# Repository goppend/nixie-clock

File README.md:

# Nixie Tube Clock (wip)

A nixie clock using IN-12 tubes, featuring a modular and efficient design.

## Todo
- [x] Port what I have to KiCad.
- [x] Fix existing problems.
- [x] Consider design changes, add last minute features, ERC.
- [x] Ensure layout is sound. DRC.
- [x] Have boards fabbed.
- [ ] (Awaiting boards/parts) Write firmware.
- [ ] Done!

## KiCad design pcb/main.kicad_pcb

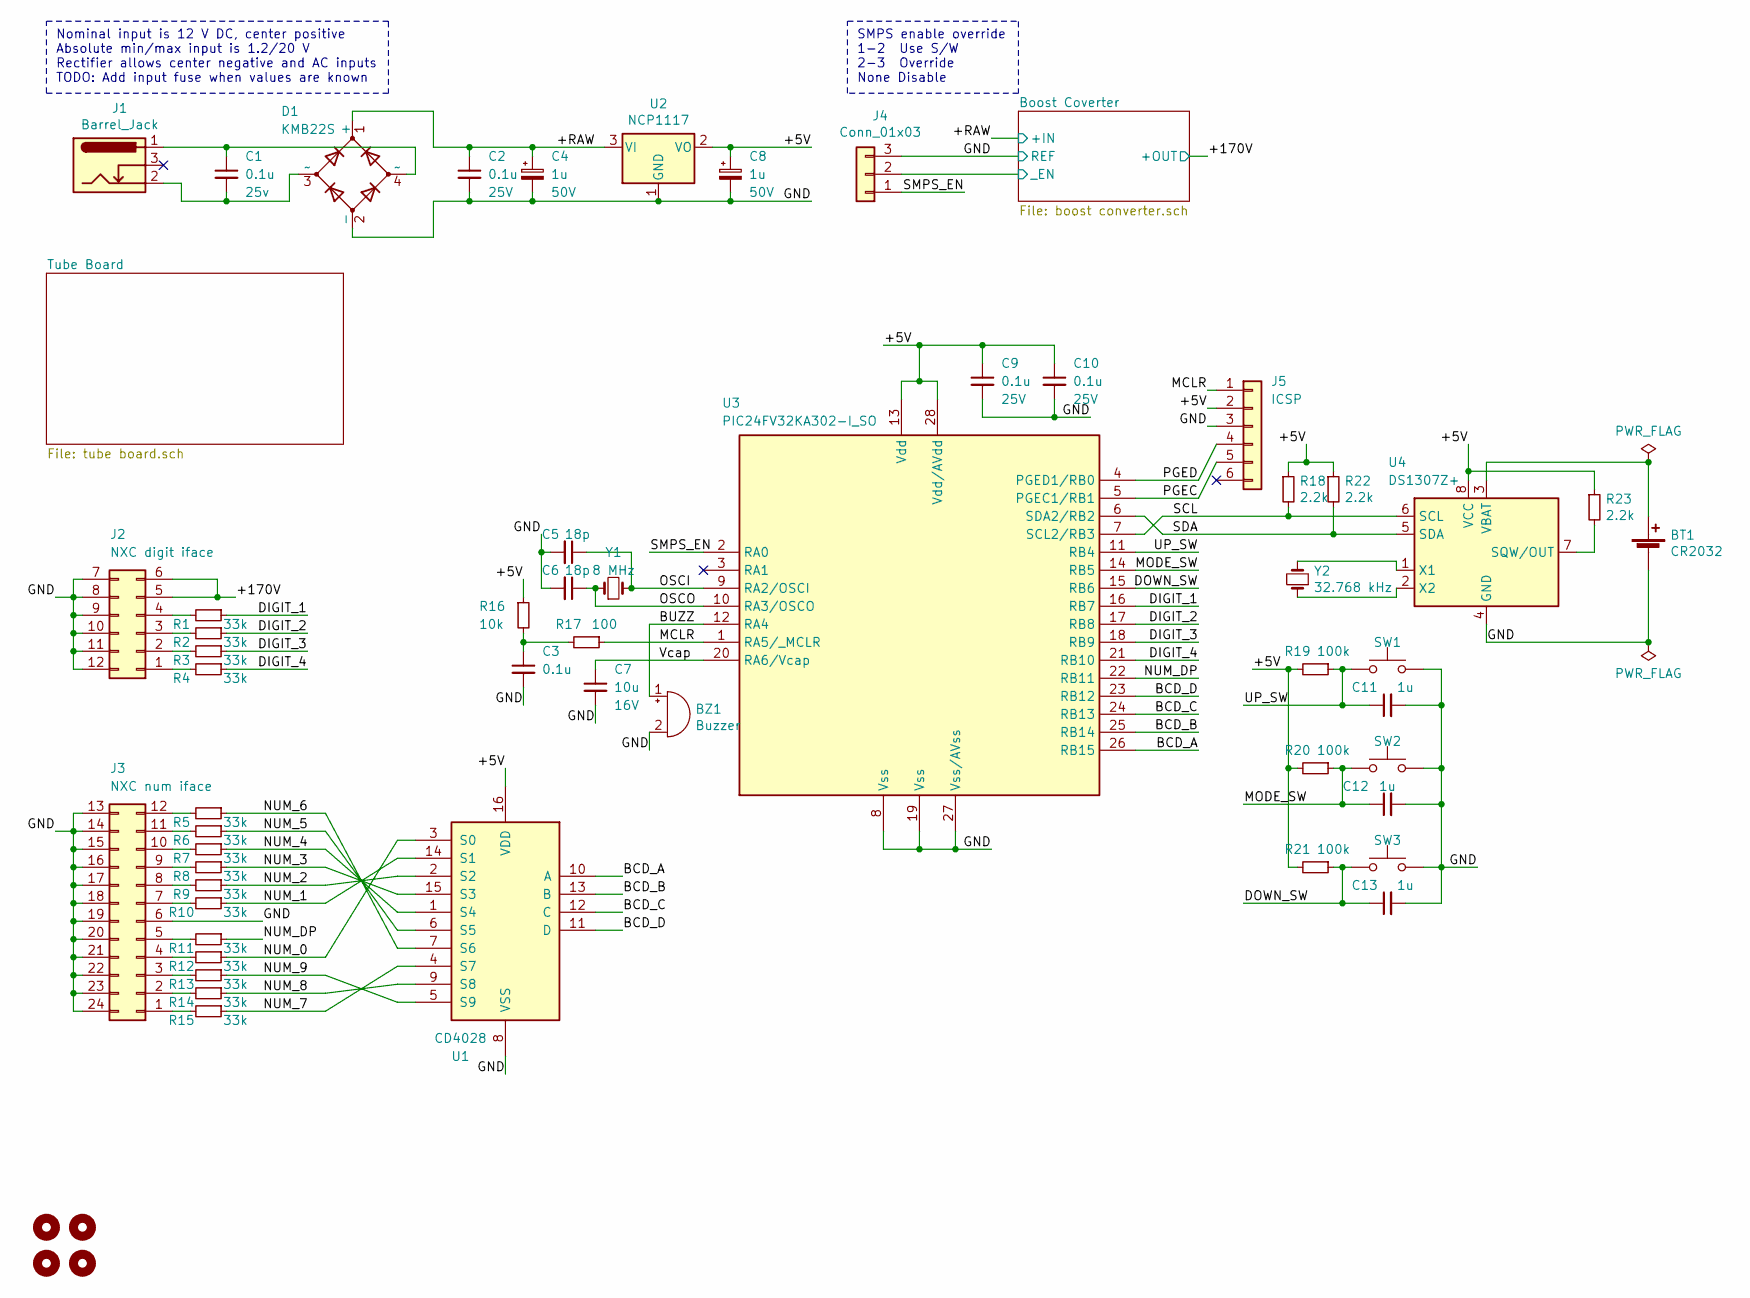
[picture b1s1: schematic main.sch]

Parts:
BT1: CR2032; BU2032SM-BT-GTR; Rating N/A
BZ1: Buzzer; Buzzer_12x9.5RM7.6; Rating 5V 50mA
C1: 0.1u; C_0805_HandSoldering; Rating 25v
C2, C3, C9, C10: 0.1u; C_0805_HandSoldering; Rating 25V
C4, C8: 1u; CP_Elec_4x5.3; Rating 50V
C5, C6: 18p; C_0805_HandSoldering; Rating 50V
C7: 10u; C_0805_HandSoldering; Rating 16V
C11, C12, C13: 1u; C_0805_HandSoldering; Rating 25V
D1: KMB22S; Diode-SMC_KMB22S-MBS; Rating 60V
H1, H2, H3, H4: MountingHole; MountingHole_3.2mm_M3; Rating N/A; Digikey Page N/A
J1: Barrel_Jack; Barrel_Jack_CUI_PJ-036AH-SMT; Rating N/A
J2: NXC digit iface; Sullins-EBC06DCWN; Rating N/A
J3: NXC num iface; Sullins-EBC12DCWN; Rating N/A
J4: Conn_01x03; Pin_Header_Straight_1x03_Pitch2.54mm; Rating N/A
J5: ICSP; Pin_Header_Straight_1x06_Pitch2.54mm; Rating N/A
R1, R2, R3, R4, R5, R6, R7, R8, R9, R10, R11, R12, R13, R14, R15: 33k; R_0805_HandSoldering; Rating 1/8W
R16: 10k; R_0805_HandSoldering; Rating 1/8W
R17: 100; R_0805_HandSoldering; Rating 1/8W
R18, R22, R23: 2.2k; R_0805_HandSoldering; Rating 1/8W
R19, R20, R21: 100k; R_0805_HandSoldering; Rating 1/8W
SW1, SW2, SW3: Tactile SPST; SW_Tactile_SPST_Angled_PTS645Vx58-2LFS; Rating N/A
U1: CD4028; SOIC-16_3.9x9.9mm_Pitch1.27mm; Rating 18V
U2: NCP1117; SOT-223-3_TabPin2; Rating 5V
U3: PIC24FV32KA302-I_SO; SOIC-28W_7.5x18.7mm_Pitch1.27mm; Rating 5V
U4: DS1307Z+; SOIC-8_3.9x4.9mm_Pitch1.27mm; Rating 5V
Y1: 8 MHz; Crystal-Abracom_ABM3-5.0x3.2; Rating ±20ppm
Y2: 32.768 kHz; Crystal-Vectron_VMK3-3.2x1.5; Rating ±20ppm

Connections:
/+5V: C8.1, C9.1, C10.1, J5.2, R16.1, R18.1, R19.2, R20.2, R21.2, R22.1, R23.1, U1.16 (VDD), U2.2 (VO), U3.13 (Vdd), U3.28 (Vdd/AVdd), U4.8 (VCC)
/+170V: J2.5, J2.6; also elsewhere on the board
/+RAW: C2.1, C4.1, D1.1 (+), U2.3 (VI); also elsewhere on the board
/BCD_A: U1.10 (A), U3.26 (RB15)
/BCD_B: U1.13 (B), U3.25 (RB14)
/BCD_C: U1.12 (C), U3.24 (RB13)
/BCD_D: U1.11 (D), U3.23 (RB12)
/BUZZ: BZ1.1 (-), U3.12 (RA4)
/Boost Coverter/_EN: J4.2; also elsewhere on the board
/DIGIT_1: R1.1, U3.16 (RB7)
/DIGIT_2: R2.1, U3.17 (RB8)
/DIGIT_3: R3.1, U3.18 (RB9)
/DIGIT_4: R4.1, U3.21 (RB10)
/DOWN_SW: C13.1, R21.1, SW3.1, U3.15 (RB6)
/GND: BT1.2 (-), BZ1.2 (+), C2.2, C3.2, C4.2, C5.2, C6.2, C7.2, C8.2, C9.2, C10.2, C11.2, C12.2, C13.2, D1.2 (-), J2.7, J2.8, J2.9, J2.10, J2.11, J2.12, J3.6, J3.13, J3.14, J3.15, J3.16, J3.17, J3.18, J3.19, J3.20, J3.21, J3.22, J3.23, J3.24, J4.3, J5.3, SW1.2, SW2.2, SW3.2, U1.8 (VSS), U2.1 (GND), U3.8 (Vss), U3.19 (Vss), U3.27 (Vss/AVss), U4.4 (GND); also elsewhere on the board
/MCLR: J5.1, R17.1, U3.1 (RA5/_MCLR)
/MODE_SW: C12.1, R20.1, SW2.1, U3.14 (RB5)
/NUM_0: R12.1, U1.3 (S0)
/NUM_1: R10.1, U1.14 (S1)
/NUM_2: R9.1, U1.2 (S2)
/NUM_3: R8.1, U1.15 (S3)
/NUM_4: R7.1, U1.1 (S4)
/NUM_5: R6.1, U1.6 (S5)
/NUM_6: R5.1, U1.7 (S6)
/NUM_7: R15.1, U1.4 (S7)
/NUM_8: R14.1, U1.9 (S8)
/NUM_9: R13.1, U1.5 (S9)
/NUM_DP: R11.1, U3.22 (RB11)
/OSCI: C5.1, U3.9 (RA2/OSCI), Y1.2
/OSCO: C6.1, U3.10 (RA3/OSCO), Y1.1
/PGEC: J5.5, U3.5 (PGEC1/RB1)
/PGED: J5.4, U3.4 (PGED1/RB0)
/SCL: R18.2, U3.7 (SCL2/RB3), U4.6 (SCL)
/SDA: R22.2, U3.6 (SDA2/RB2), U4.5 (SDA)
/SMPS_EN: J4.1, U3.2 (RA0)
/UP_SW: C11.1, R19.1, SW1.1, U3.11 (RB4)
/Vcap: C7.1, U3.20 (RA6/Vcap)
unnamed: BT1.1 (+), U4.3 (VBAT)
unnamed: C1.1, D1.4 (~~), J1.1
unnamed: C1.2, D1.3 (~~), J1.2
unnamed: C3.1, R16.2, R17.2
unnamed: J2.1, R4.2
unnamed: J2.2, R3.2
unnamed: J2.3, R2.2
unnamed: J2.4, R1.2
unnamed: J3.1, R15.2
unnamed: J3.2, R14.2
unnamed: J3.3, R13.2
unnamed: J3.4, R12.2
unnamed: J3.5, R11.2
unnamed: J3.7, R10.2
unnamed: J3.8, R9.2
unnamed: J3.9, R8.2
unnamed: J3.10, R7.2
unnamed: J3.11, R6.2
unnamed: J3.12, R5.2
unnamed: R23.2, U4.7 (SQW/OUT)
unnamed: U4.1 (X1), Y2.2
unnamed: U4.2 (X2), Y2.1

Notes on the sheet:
SMPS enable override 1-2 Use S/W 2-3 Override None Disable
Nominal input is 12 V DC, center positive Absolute min/max input is 1.2/20 V Rectifier allows center negative and AC inputs TODO: Add input fuse when values are known

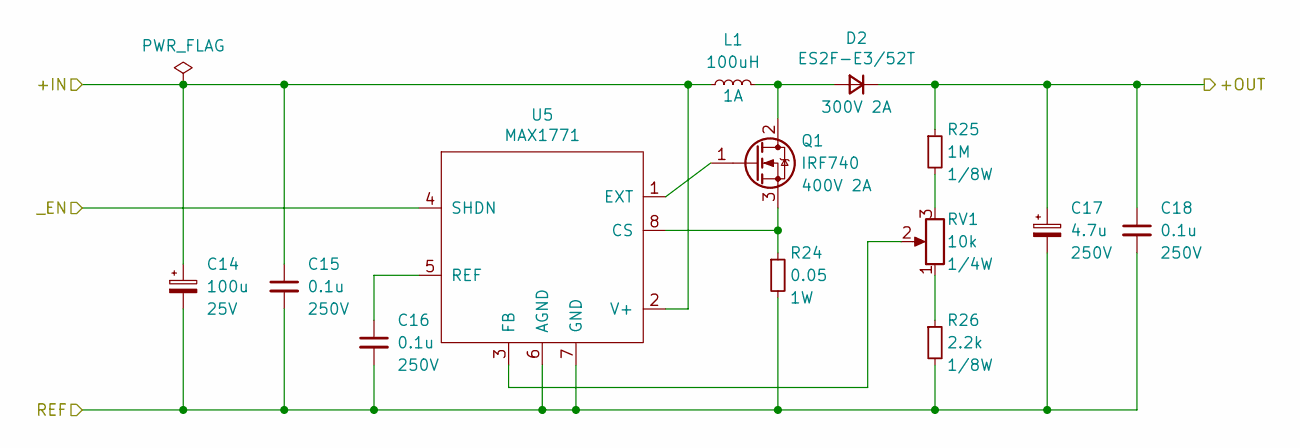
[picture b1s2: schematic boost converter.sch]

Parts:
C14: 100u; CP_Elec_6.3x5.8; Rating 25V
C15, C16: 0.1u; C_0805_HandSoldering; Rating 250V
C17: 4.7u; CP_Radial_D10.0mm_P5.00mm; Rating 250V
C18: 0.1u; C_1206_HandSoldering; Rating 250V
D2: ES2F-E3/52T; D_SMB_Handsoldering; Rating 300V 2A
L1: 100uH; Inductor_Taiyo-Yuden_NR-80xx_HandSoldering; Rating 1A
Q1: IRF740; TO-263-2; Rating 400V 2A
R24: 0.05; R_1206_HandSoldering; Rating 1W
R25: 1M; R_0805_HandSoldering; Rating 1/8W
R26: 2.2k; R_0805_HandSoldering; Rating 1/8W
RV1: 10k; Potentiometer_Trimmer_Bourns_3214X; Rating 1/4W
U5: MAX1771; SOIC-8_3.9x4.9mm_Pitch1.27mm; Rating 16.5V

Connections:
/+170V: C17.1, C18.1, D2.1 (K), R25.1; also elsewhere on the board
/+RAW: C14.1, C15.1, L1.1, U5.2 (V+); also elsewhere on the board
/Boost Coverter/_EN: U5.4 (SHDN); also elsewhere on the board
/GND: C14.2, C15.2, C16.2, C17.2, C18.2, R24.2, R26.2, U5.6 (AGND), U5.7 (GND); also elsewhere on the board
unnamed: C16.1, U5.5 (REF)
unnamed: D2.2 (A), L1.2, Q1.2 (D)
unnamed: Q1.1 (G), U5.1 (EXT)
unnamed: Q1.3 (S), R24.1, U5.8 (CS)
unnamed: R25.2, RV1.3
unnamed: R26.1, RV1.1
unnamed: RV1.2, U5.3 (FB)

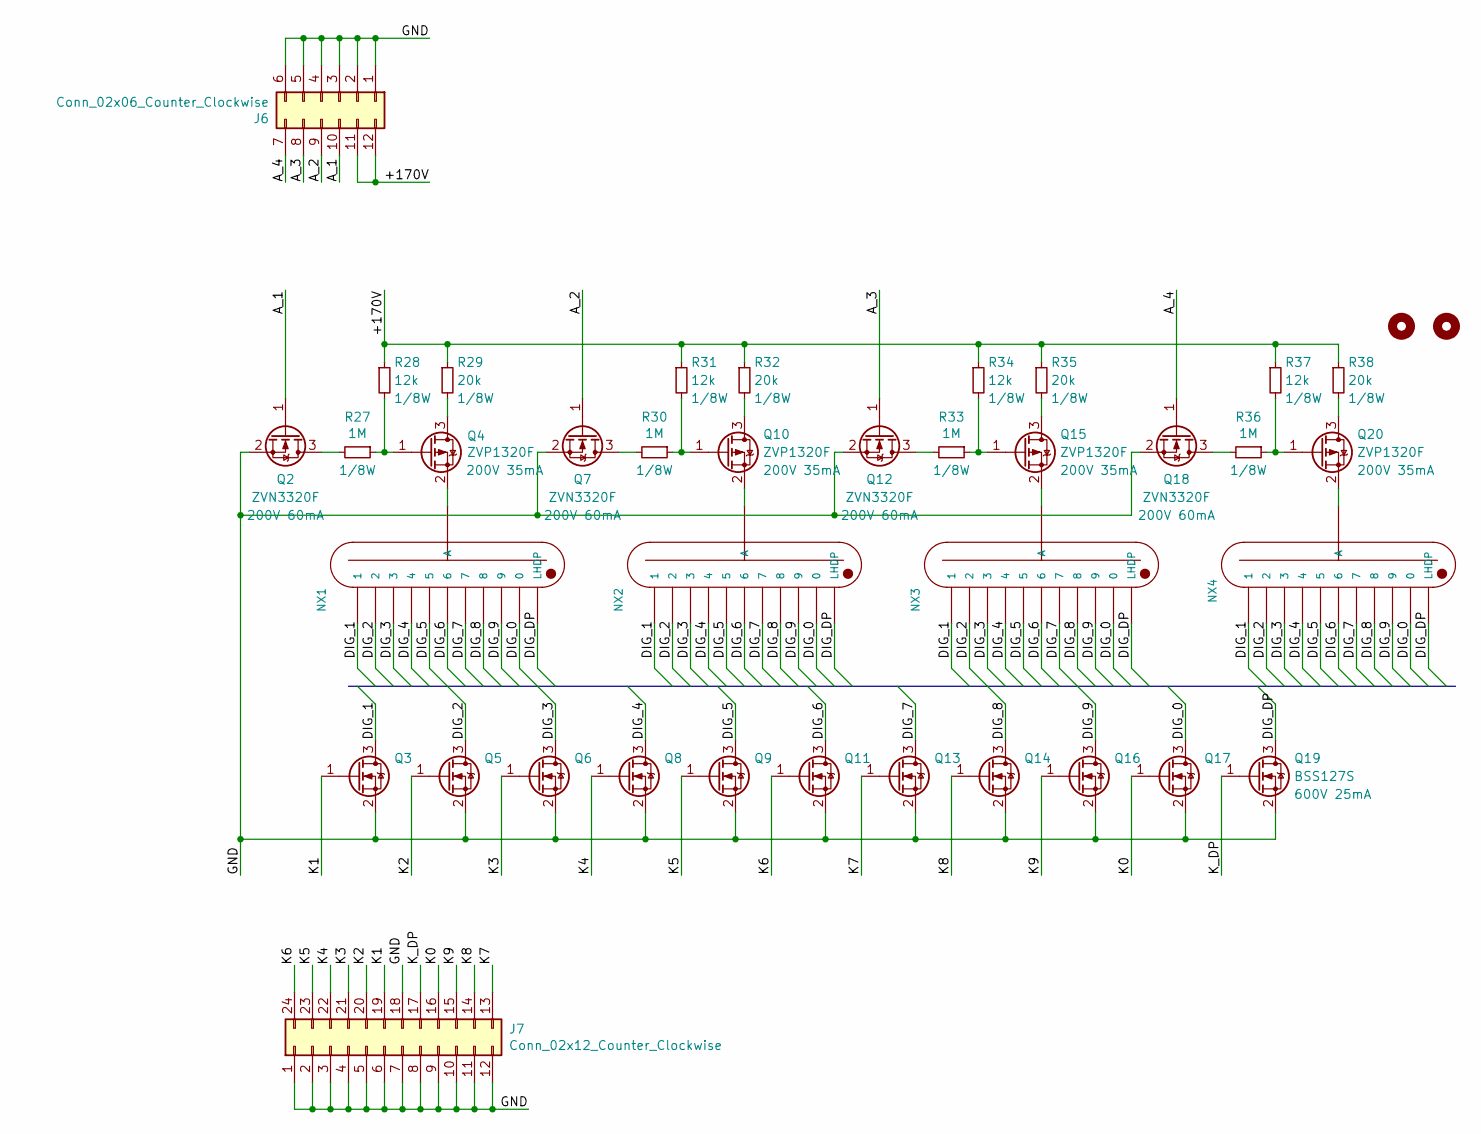
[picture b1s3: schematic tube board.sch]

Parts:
H5, H6: 3mm; MountingHole_3mm; Rating N/A; Digikey Page N/A
J6: Conn_02x06_Counter_Clockwise; Sullins-EBC06DCWN-Mating-Edge; Rating N/A; Digikey Page N/A
J7: Conn_02x12_Counter_Clockwise; Sullins-EBC12DCWN-Mating-Edge; Rating N/A; Digikey Page N/A
NX1, NX2, NX3, NX4: IN-12A; IN-12-Socket; Rating 170V; Digikey Page N/A
Q2, Q7, Q12, Q18: ZVN3320F; SOT-23; Rating 200V 60mA
Q3, Q5, Q6, Q8, Q9, Q11, Q13, Q14, Q16, Q17, Q19: BSS127S; SOT-23; Rating 600V 25mA
Q4, Q10, Q15, Q20: ZVP1320F; SOT-23; Rating 200V 35mA
R27, R30, R33, R36: 1M; R_0805; Rating 1/8W
R28, R31, R34, R37: 12k; R_0805; Rating 1/8W
R29, R32, R35, R38: 20k; R_0805; Rating 1/8W

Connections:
/Tube Board/+170V: J6.11, J6.12, R28.1, R29.1, R31.1, R32.1, R34.1, R35.1, R37.1, R38.1
/Tube Board/A_1: J6.10, Q2.1 (G)
/Tube Board/A_2: J6.9, Q7.1 (G)
/Tube Board/A_3: J6.8, Q12.1 (G)
/Tube Board/A_4: J6.7, Q18.1 (G)
/Tube Board/DIG_0: NX1.0, NX2.0, NX3.0, NX4.0, Q17.3 (D)
/Tube Board/DIG_1: NX1.1, NX2.1, NX3.1, NX4.1, Q3.3 (D)
/Tube Board/DIG_2: NX1.2, NX2.2, NX3.2, NX4.2, Q5.3 (D)
/Tube Board/DIG_3: NX1.3, NX2.3, NX3.3, NX4.3, Q6.3 (D)
/Tube Board/DIG_4: NX1.4, NX2.4, NX3.4, NX4.4, Q8.3 (D)
/Tube Board/DIG_5: NX1.5, NX2.5, NX3.5, NX4.5, Q9.3 (D)
/Tube Board/DIG_6: NX1.6, NX2.6, NX3.6, NX4.6, Q11.3 (D)
/Tube Board/DIG_7: NX1.7, NX2.7, NX3.7, NX4.7, Q13.3 (D)
/Tube Board/DIG_8: NX1.8, NX2.8, NX3.8, NX4.8, Q14.3 (D)
/Tube Board/DIG_9: NX1.9, NX2.9, NX3.9, NX4.9, Q16.3 (D)
/Tube Board/DIG_DP: NX1.LHDP, NX2.LHDP, NX3.LHDP, NX4.LHDP, Q19.3 (D)
/Tube Board/GND: J6.1, J6.2, J6.3, J6.4, J6.5, J6.6, J7.1, J7.2, J7.3, J7.4, J7.5, J7.6, J7.7, J7.8, J7.9, J7.10, J7.11, J7.12, J7.18, Q2.2 (S), Q3.2 (S), Q5.2 (S), Q6.2 (S), Q7.2 (S), Q8.2 (S), Q9.2 (S), Q11.2 (S), Q12.2 (S), Q13.2 (S), Q14.2 (S), Q16.2 (S), Q17.2 (S), Q18.2 (S), Q19.2 (S)
/Tube Board/K0: J7.16, Q17.1 (G)
/Tube Board/K1: J7.19, Q3.1 (G)
/Tube Board/K2: J7.20, Q5.1 (G)
/Tube Board/K3: J7.21, Q6.1 (G)
/Tube Board/K4: J7.22, Q8.1 (G)
/Tube Board/K5: J7.23, Q9.1 (G)
/Tube Board/K6: J7.24, Q11.1 (G)
/Tube Board/K7: J7.13, Q13.1 (G)
/Tube Board/K8: J7.14, Q14.1 (G)
/Tube Board/K9: J7.15, Q16.1 (G)
/Tube Board/K_DP: J7.17, Q19.1 (G)
unnamed: NX1.A, Q4.2 (S)
unnamed: NX2.A, Q10.2 (S)
unnamed: NX3.A, Q15.2 (S)
unnamed: NX4.A, Q20.2 (S)
unnamed: Q2.3 (D), R27.2
unnamed: Q4.1 (G), R27.1, R28.2
unnamed: Q4.3 (D), R29.2
unnamed: Q7.3 (D), R30.2
unnamed: Q10.1 (G), R30.1, R31.2
unnamed: Q10.3 (D), R32.2
unnamed: Q12.3 (D), R33.2
unnamed: Q15.1 (G), R33.1, R34.2
unnamed: Q15.3 (D), R35.2
unnamed: Q18.3 (D), R36.2
unnamed: Q20.1 (G), R36.1, R37.2
unnamed: Q20.3 (D), R38.2

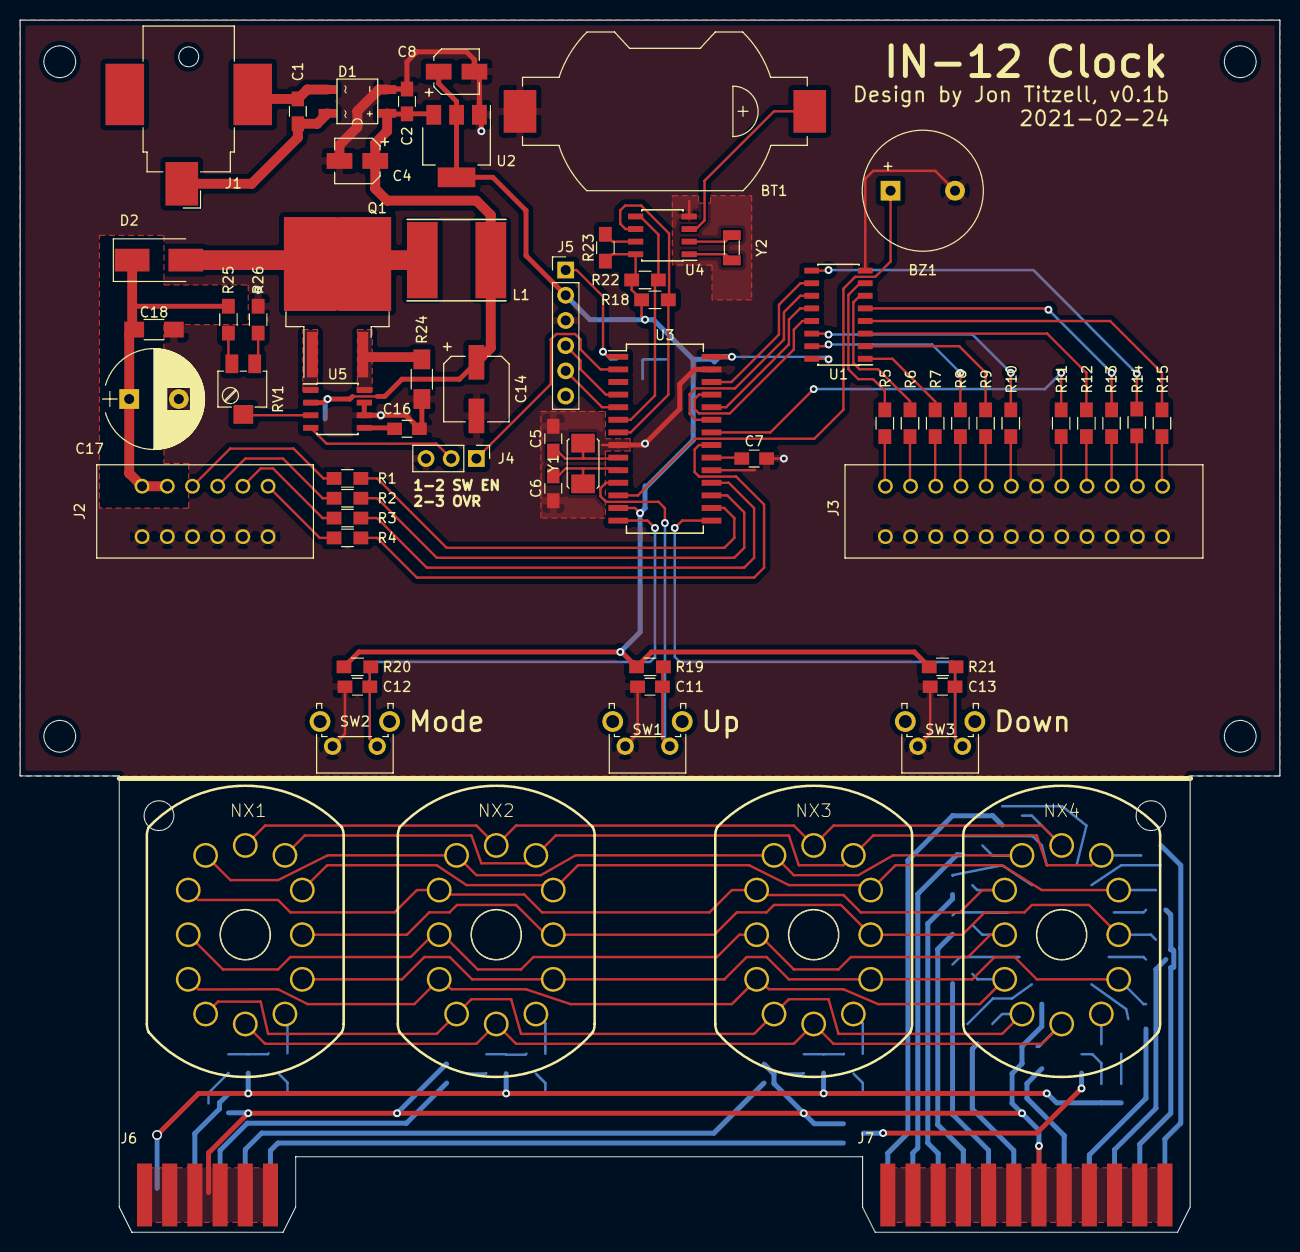
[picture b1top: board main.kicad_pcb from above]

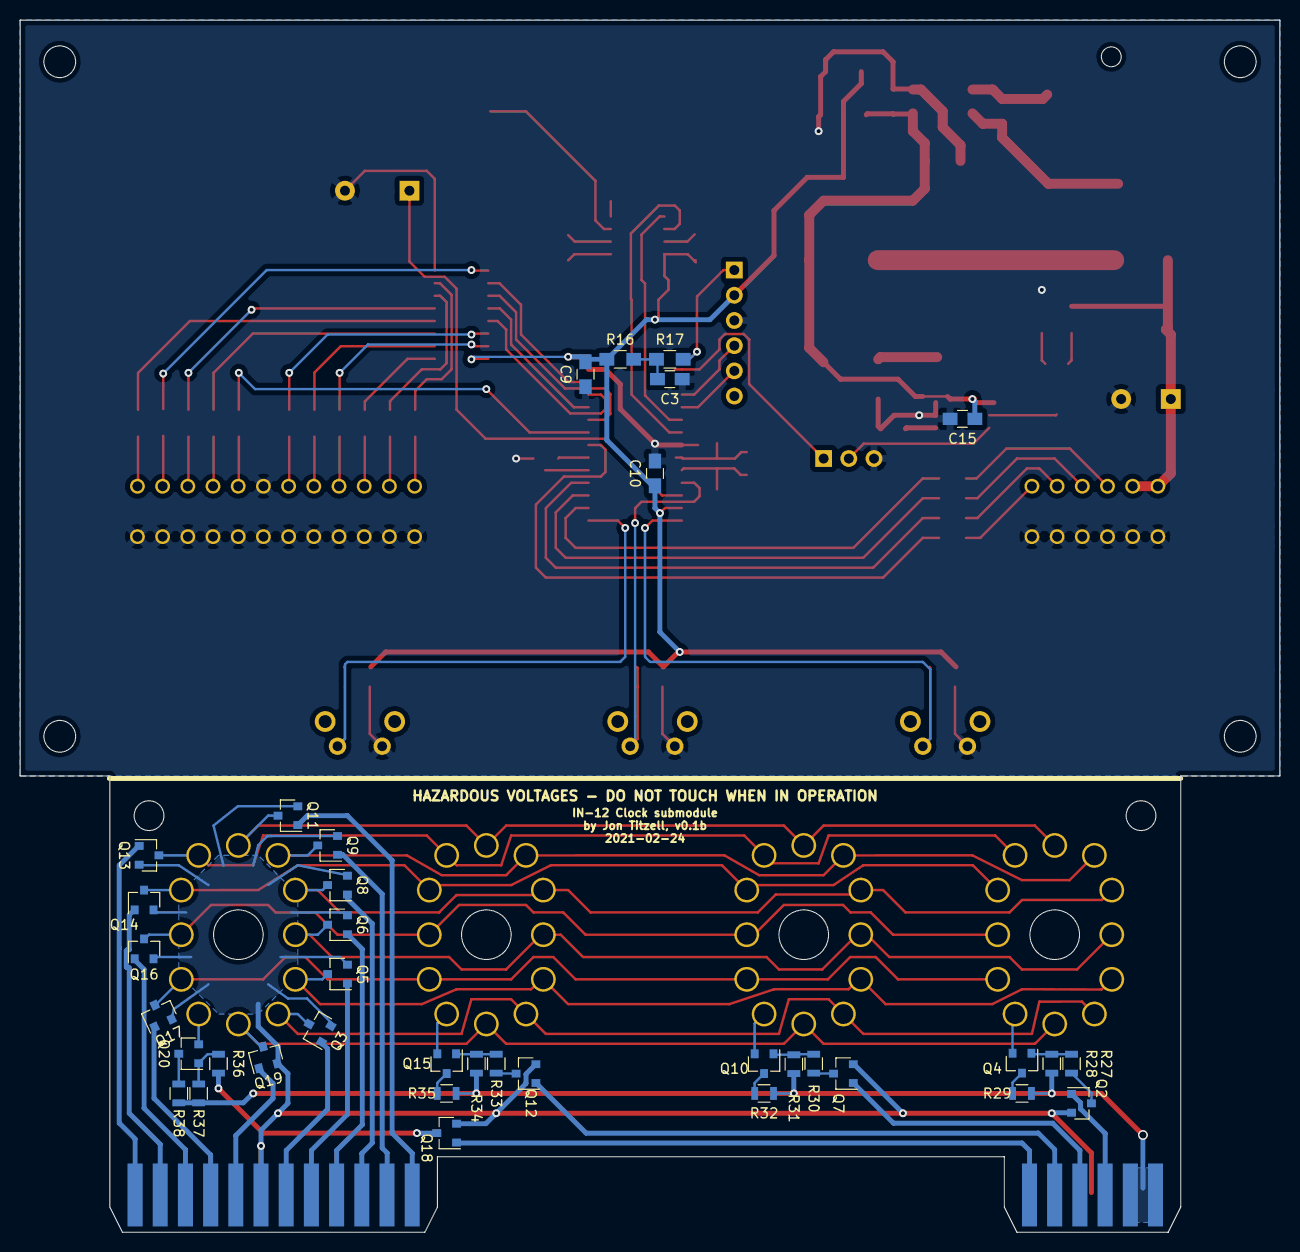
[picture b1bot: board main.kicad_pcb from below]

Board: 2 copper layers, 127.0 x 122.2 mm, 109 parts (37 on the bottom side), 110 nets.

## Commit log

2022-01-19 Add old project files to repo
2022-01-30 Remove old DesignSpark project, recreate it with KiCad.
2022-02-02 Update PCB and schematic files with mostly small tweaks. Added DRC rules added to .pro, and changes on layout and footprints to reflect that.
2022-02-04 Add alternate parts for BOM, adjust micro to be more compatible with new PIC24FJ series parts.
2022-02-07 Update schematic with some better part selection, reducing BOM. Update PCB for panelized fabrication.
2022-02-24 Fix some problems with pcb, crystals and rectifier using wrong footprints. Octal decoder had Vss and Vdd swapped.
2022-02-24 Update board to reflect new crystal and rectifier footprint. Update silkscreen ver/date, add new board renders and schematic plots.
